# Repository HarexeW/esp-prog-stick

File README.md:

# ESP-PROG Stick

Project Documentation moved to [harexew.com](https://harexew.com/esp-prog-stick)

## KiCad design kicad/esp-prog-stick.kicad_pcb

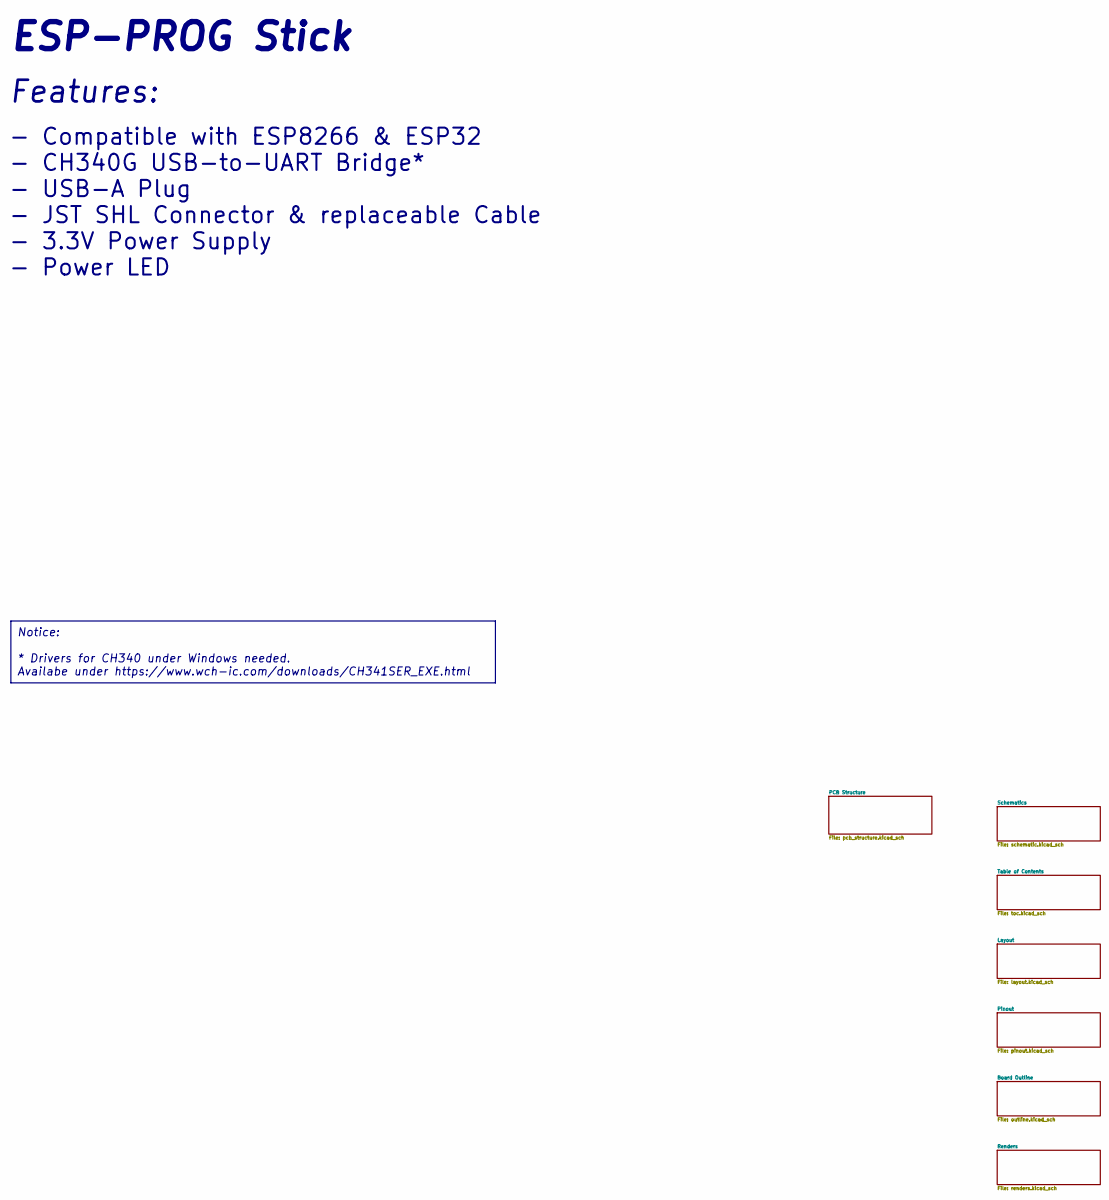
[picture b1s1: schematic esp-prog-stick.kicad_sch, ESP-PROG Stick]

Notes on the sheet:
Notice: * Drivers for CH340 under Windows needed. Availabe under https://www.wch-ic.com/downloads/CH341SER_EXE.html
- Compatible with ESP8266 & ESP32 - CH340G USB-to-UART Bridge* - USB-A Plug - JST SHL Connector & replaceable Cable - 3.3V Power Supply - Power LED
ESP-PROG Stick
Features:

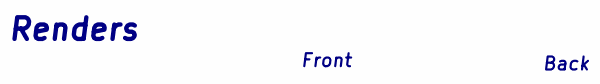
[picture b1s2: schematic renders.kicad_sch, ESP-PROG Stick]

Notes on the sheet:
Front
Renders
Back

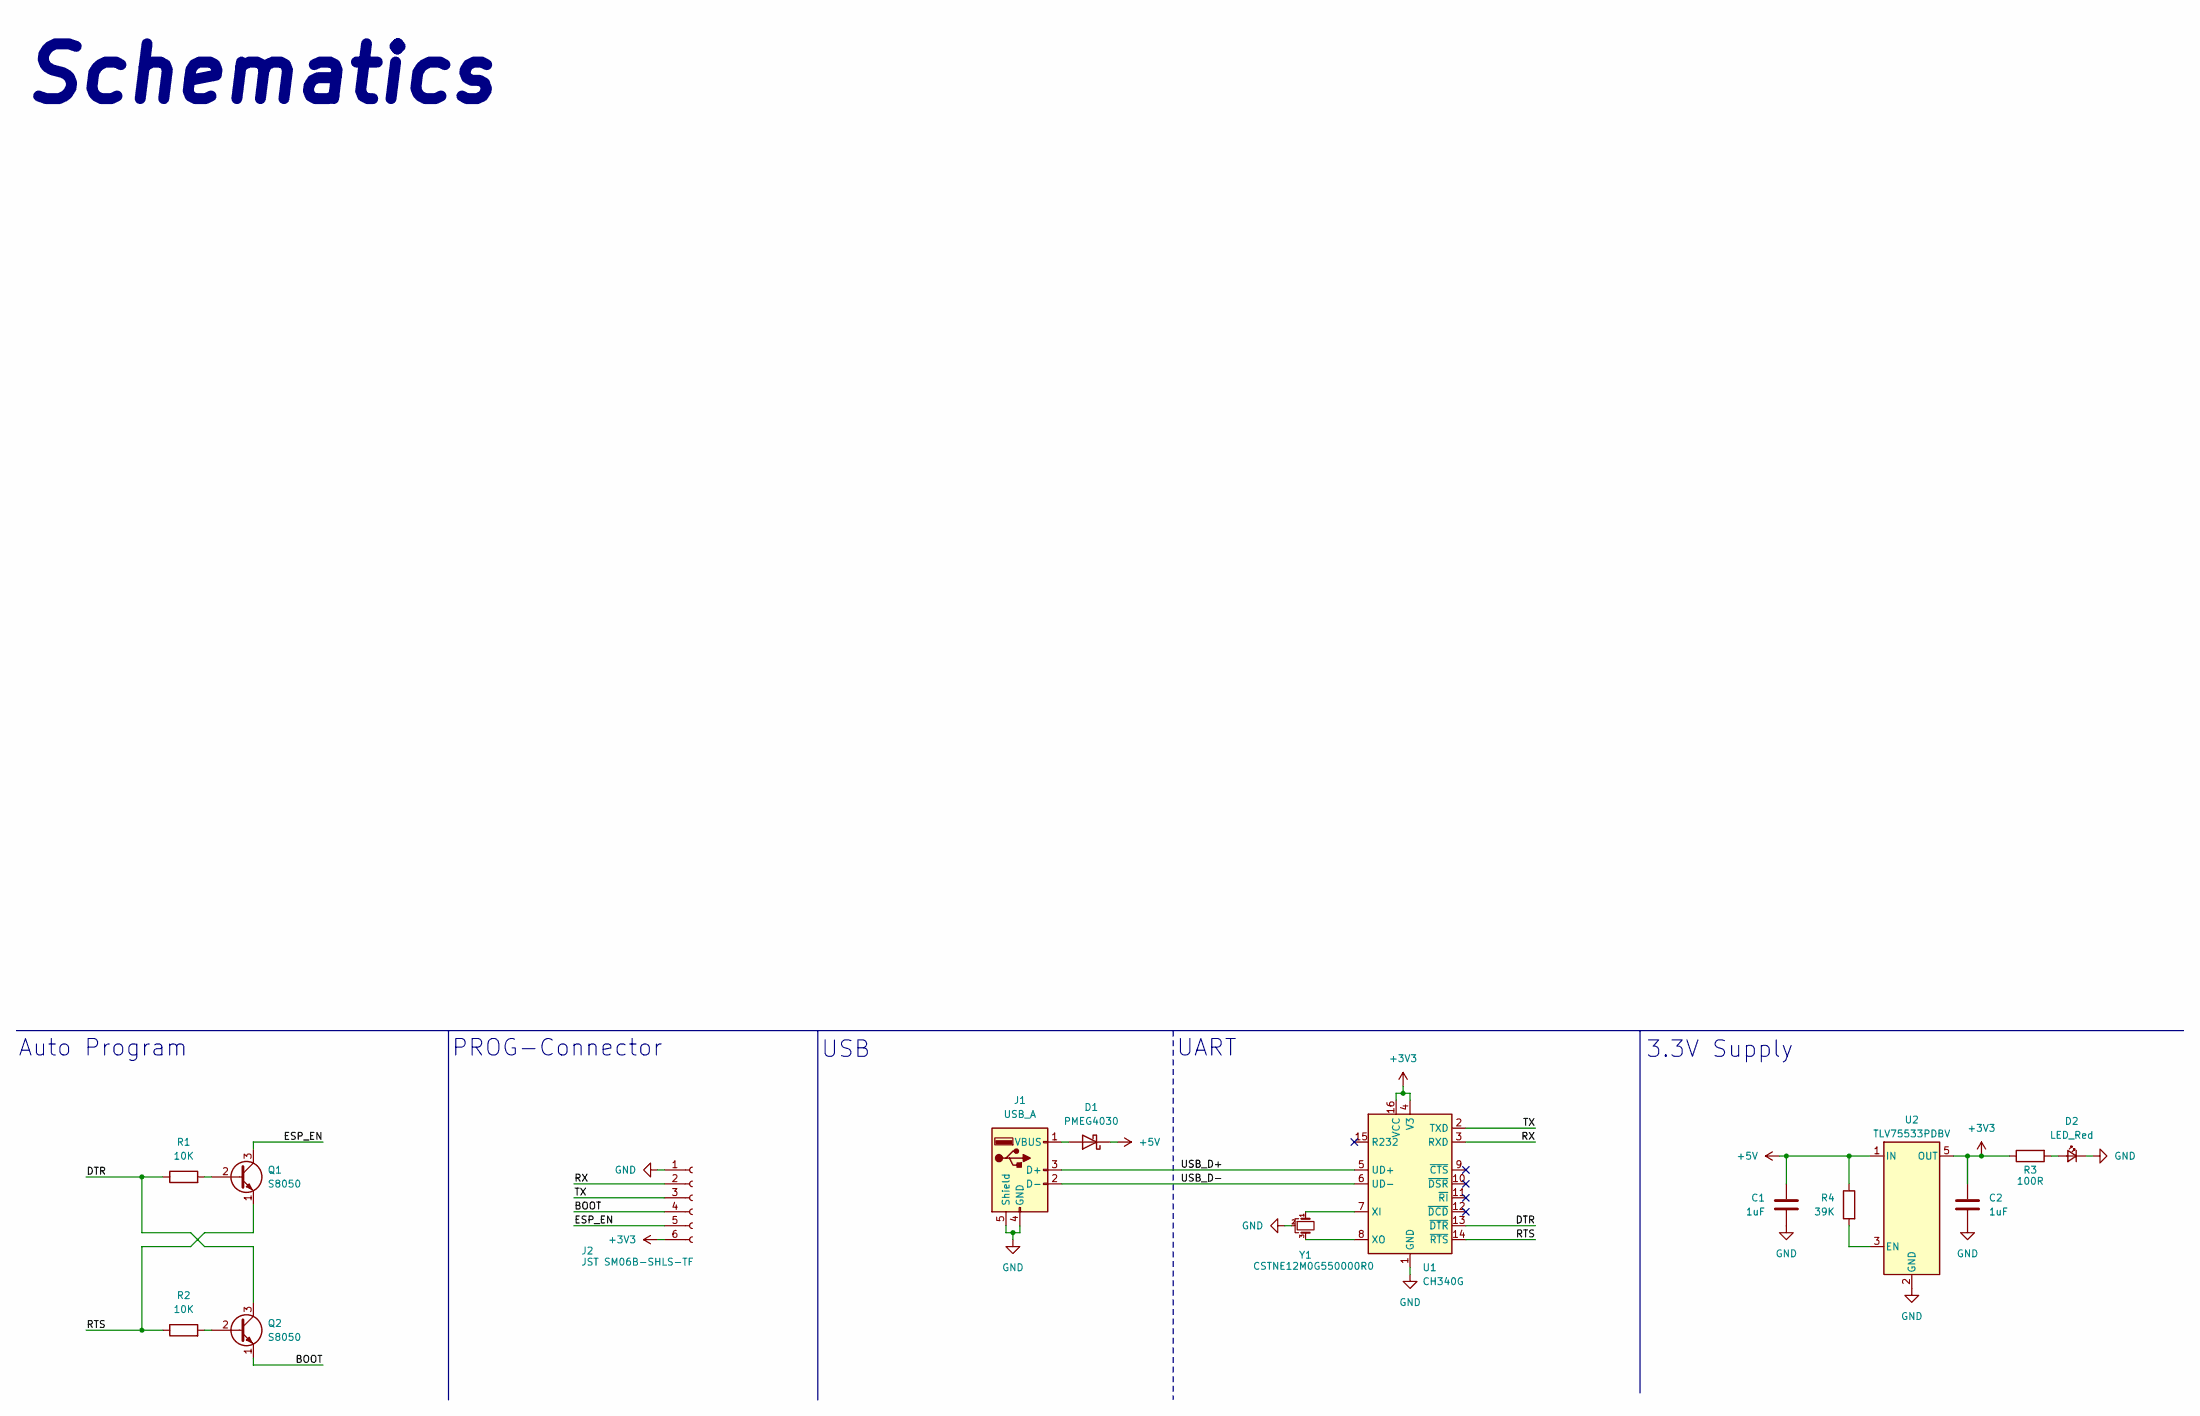
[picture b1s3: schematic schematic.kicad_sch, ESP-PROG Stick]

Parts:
C1, C2: 1uF; C_0603_1608Metric_Pad1.08x0.95mm_HandSolder; Part CL10A105KB8NNNC
D1: PMEG4030; D_SOD-123; Part PMEG4030ER115
D2: LED_Red; LED_0603_1608Metric_Pad1.05x0.95mm_HandSolder; Part SML-D15VWT86C
J1: USB_A; XKB_U217-041N; Part 100101101101
J2: JST SM06B-SHLS-TF; JST_SHL_SM06B-SHLS-TF_1x06-1MP_P1.00mm_Horizontal; Part SM06BSHLSTFLFSN
Q1, Q2: S8050; SOT-23; Part S8050
R1, R2: 10K; R_0603_1608Metric; Part RC0603FR1310KL
R3: 100R; R_0603_1608Metric; Part RC0603FR-07100RL
R4: 39K; R_0603_1608Metric_Pad0.98x0.95mm_HandSolder; Part RT0603BRD0739KL
U1: CH340G; SOIC-16_3.9x9.9mm_P1.27mm; Part CH340G
U2: TLV75533PDBV; SOT-23-5; Part TLV75533PDBV
Y1: CSTNE12M0G550000R0; Resonator_SMD_Murata_CSTxExxV-3Pin_3.0x1.1mm; Part CSTNE12M0G550000R0

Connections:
+3V3: C2.2, J2.6, R3.1, U1.4 (V3), U1.16 (VCC), U2.5 (OUT)
+5V: C1.2, D1.1 (K), R4.1, U2.1 (IN)
/Schematics/BOOT: J2.4, Q2.1 (E)
/Schematics/DTR: Q2.3 (C), R1.1, U1.13 (~DTR)
/Schematics/ESP_EN: J2.5, Q1.3 (C)
/Schematics/RTS: Q1.1 (E), R2.1, U1.14 (~RTS)
/Schematics/RX: J2.2, U1.3 (RXD)
/Schematics/TX: J2.3, U1.2 (TXD)
/Schematics/USB_D+: J1.3 (D+), U1.5 (UD+)
/Schematics/USB_D-: J1.2 (D-), U1.6 (UD-)
GND: C1.1, C2.1, D2.1 (K), J1.4 (GND), J1.5 (Shield), J2.1, U1.1 (GND), U2.2 (GND), Y1.2
unnamed: D1.2 (A), J1.1 (VBUS)
unnamed: D2.2 (A), R3.2
unnamed: Q1.2 (B), R1.2
unnamed: Q2.2 (B), R2.2
unnamed: U1.7 (XI), Y1.1
unnamed: U1.8 (XO), Y1.3
unnamed: R4.2, U2.3 (EN)

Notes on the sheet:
Auto Program
3.3V Supply
UART
Schematics
USB
PROG-Connector

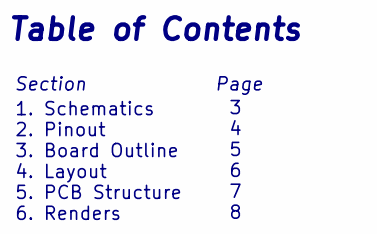
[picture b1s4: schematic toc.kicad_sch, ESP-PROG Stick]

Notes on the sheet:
3 4 5 6 7 8
1. Schematics 2. Pinout 3. Board Outline 4. Layout 5. PCB Structure 6. Renders
Table of Contents
Section Page

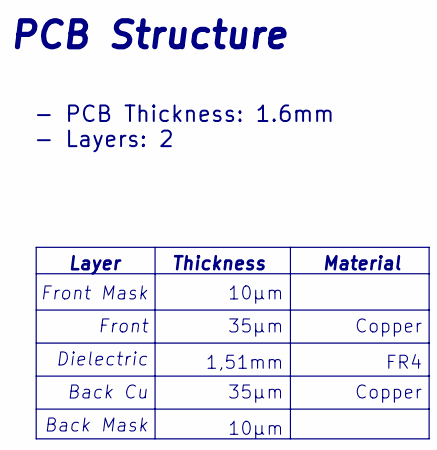
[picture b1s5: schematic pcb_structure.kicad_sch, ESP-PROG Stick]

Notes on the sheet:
Back Mask
10µm
Back Cu
Material
Dielectric
35µm
FR4
PCB Structure
Layer
Front Mask
- PCB Thickness: 1.6mm - Layers: 2
Copper
1,51mm
Front
Thickness

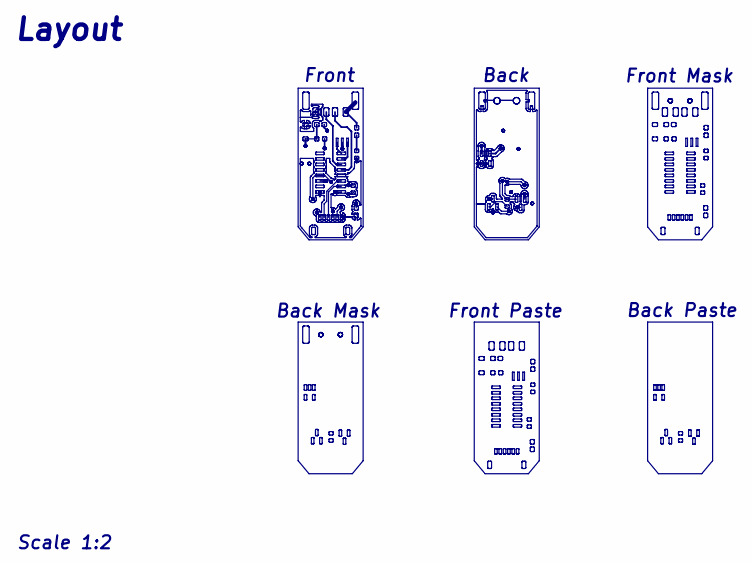
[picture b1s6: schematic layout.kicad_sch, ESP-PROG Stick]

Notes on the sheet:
Back
Layout
Front Paste
Scale 1:2
Front
Front Mask
Back Paste
Back Mask

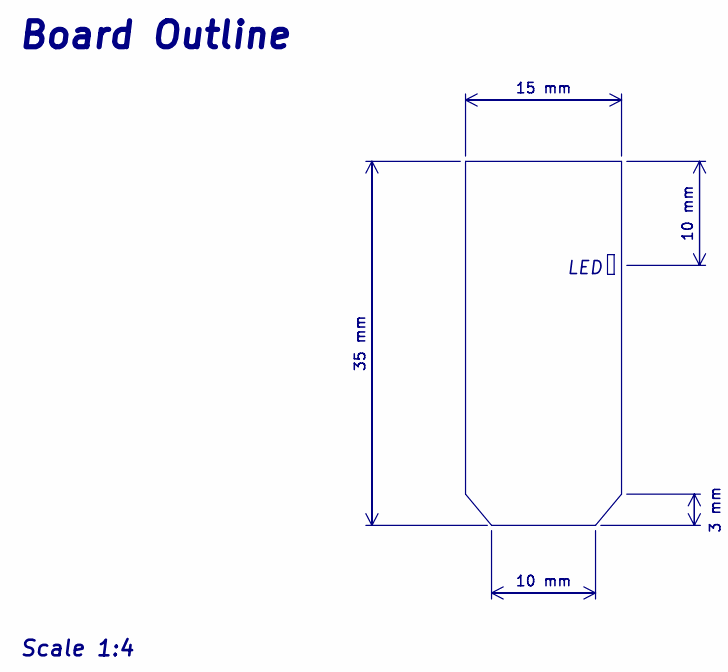
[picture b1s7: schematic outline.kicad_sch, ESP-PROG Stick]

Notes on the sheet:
Scale 1:4
LED
Board Outline

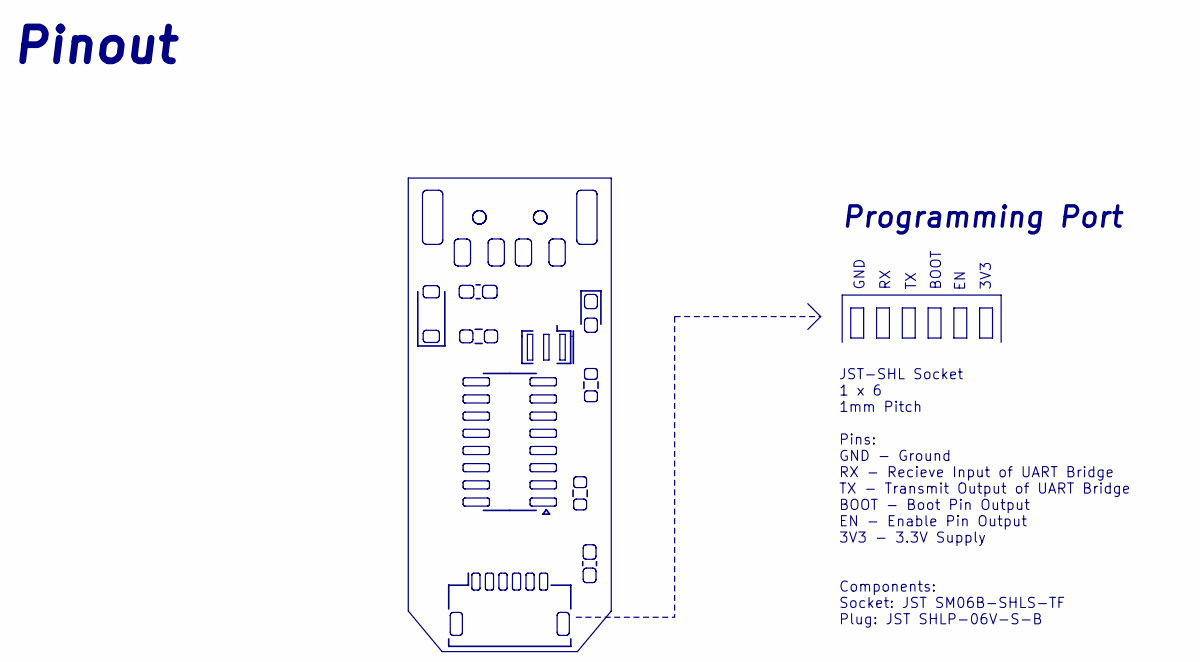
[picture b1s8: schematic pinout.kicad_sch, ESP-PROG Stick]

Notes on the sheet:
Programming Port
BOOT
3V3
GND
JST-SHL Socket 1 x 6 1mm Pitch Pins: GND - Ground RX - Recieve Input of UART Bridge TX - Transmit Output of UART Bridge BOOT - Boot Pin Output EN - Enable Pin Output 3V3 - 3.3V Supply Components: Socket: JST SM06B-SHLS-TF Plug: JST SHLP-06V-S-B
Pinout

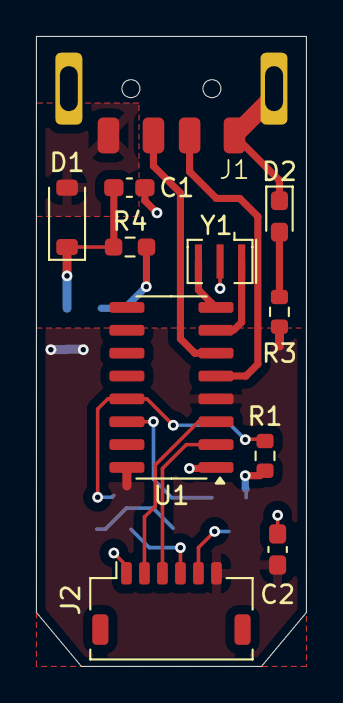
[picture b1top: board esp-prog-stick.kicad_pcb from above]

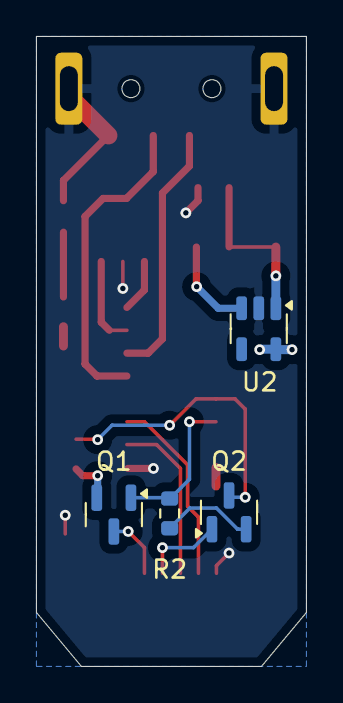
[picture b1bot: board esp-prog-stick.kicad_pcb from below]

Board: 2 copper layers, 15.0 x 35.0 mm, 15 parts (4 on the bottom side), 18 nets.

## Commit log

2024-10-31 Updates readme
2024-10-31 Updated readme again...
2024-10-31 Updated Schematic and BOM File
2024-10-31 Small update
2024-12-24 Revision 2
2024-12-24 Changed readme
